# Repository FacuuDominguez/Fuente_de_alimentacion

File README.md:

# Fuente de Alimentación Regulable

 Esta Fuente de Alimentación hecha de manera casera integra de manera embebida un modulo **LM2596** y un **puente rectificador de diodos** haciendo posible la conversión de AC a DC, todo en una misma placa **doble faz** aplicando conocimientos de Electronica tanto de **Corriente Alterna** como **Corriente Continua** 

 ## Caracteristicas

- Integra un modulo LM2596 **Embebido**

- Un puente rectificador de diodos

- Placa de doble cara o **doble faz**

- La tensión que regula es de **1,25V** hasta **20V** DC

- Corriente maxima de salida de **2 A**

- Protección contra inversión de polaridad

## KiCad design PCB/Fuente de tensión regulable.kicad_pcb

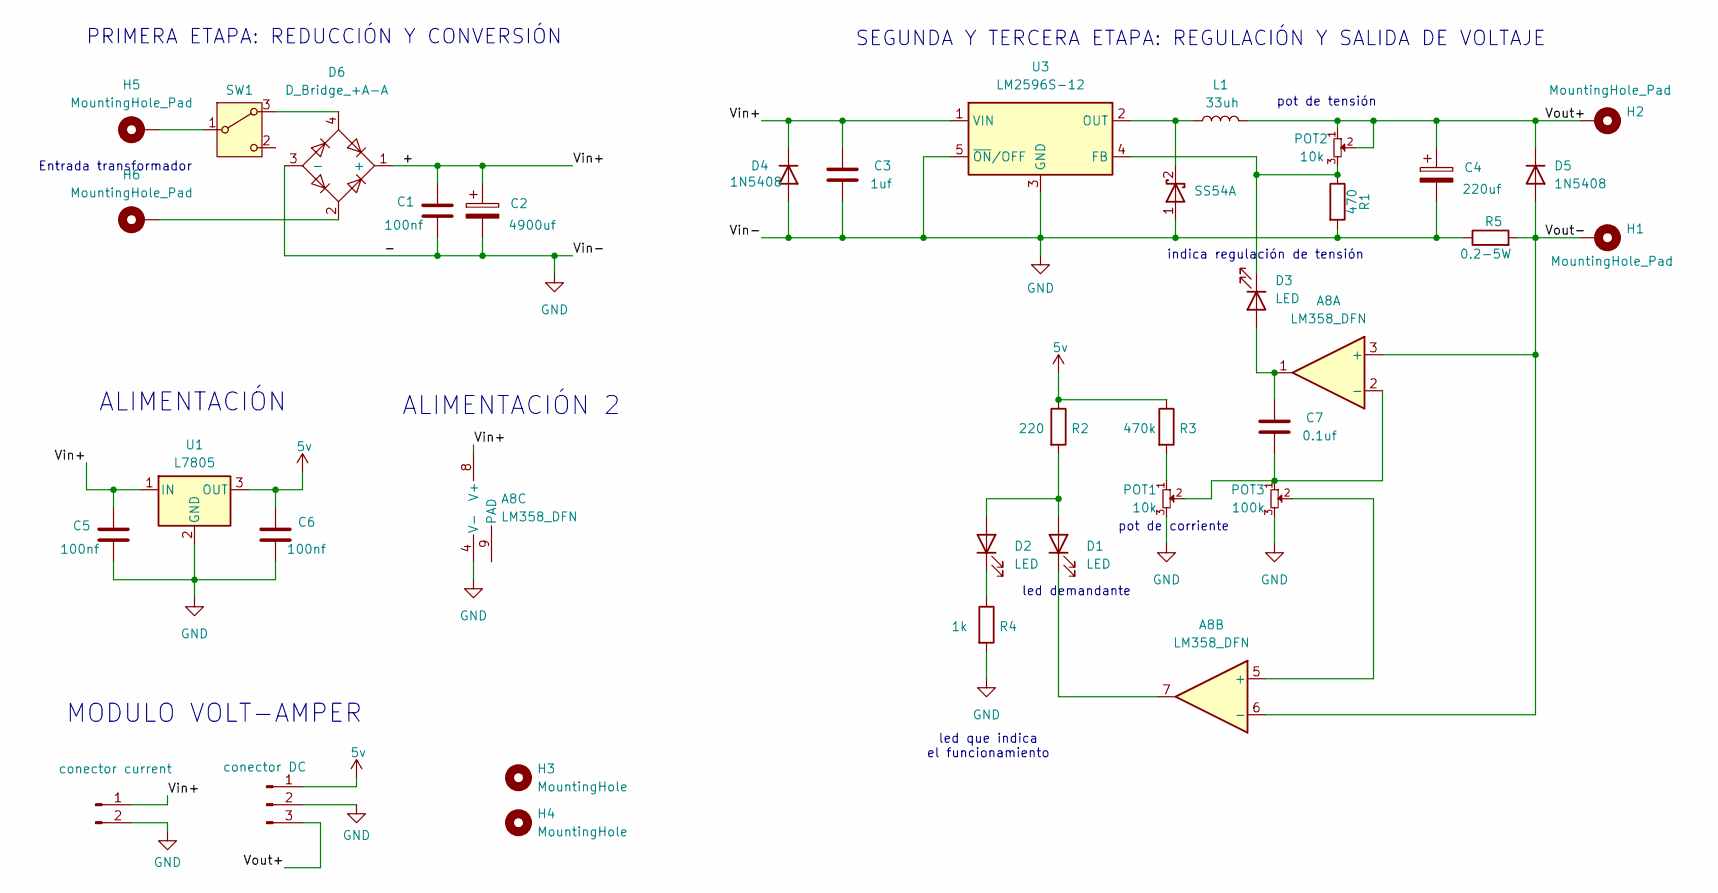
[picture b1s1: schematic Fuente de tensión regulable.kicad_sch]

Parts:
A8: LM358_DFN; Texas_HSOP-8-1EP_3.9x4.9mm_P1.27mm
C1, C5, C6: 100nf; C_0805_2012Metric_Pad1.18x1.45mm_HandSolder
C2: 4900uf; CP_Radial_D22.0mm_P10.00mm_SnapIn
C3: 1uf; C_0805_2012Metric_Pad1.18x1.45mm_HandSolder
C4: 220uf; CP_Elec_10x7.9
C7: 0.1uf; C_0805_2012Metric_Pad1.18x1.45mm_HandSolder
D1, D2, D3: LED; LED_D5.0mm
D4, D5: 1N5408; D_DO-201AE_P5.08mm_Vertical_AnodeUp
D6: D_Bridge_+A-A; Diode_bridge
H1, H2: MountingHole_Pad; MountingHole_2.5mm_Pad
H3, H4: MountingHole; MountingHole_3.2mm_M3_DIN965
H5, H6: MountingHole_Pad; TestPoint_Pad_3.0x3.0mm
J2: conector DC; JST_EH_B3B-EH-A_1x03_P2.50mm_Vertical
J3: conector current; JST_EH_B2B-EH-A_1x02_P2.50mm_Vertical
L1: 33uh; L_Bourns_SRR1260
POT1, POT2: 10k; PinHeader_1x03_P2.54mm_Vertical
POT3: 100k; PinHeader_1x03_P2.54mm_Vertical
R1: 470; R_0805_2012Metric_Pad1.20x1.40mm_HandSolder
R2: 220; R_0805_2012Metric_Pad1.20x1.40mm_HandSolder
R3: 470k; R_0805_2012Metric_Pad1.20x1.40mm_HandSolder
R4: 1k; R_0805_2012Metric_Pad1.20x1.40mm_HandSolder
R5: 0.2-5W; R_Axial_DIN0414_L11.9mm_D4.5mm_P15.24mm_Horizontal
SS54: D_Schottky_Dual_CommonAnode_AKK_Split; D_SMA
SW1: SW_Wuerth_450301014042; PinHeader_1x03_P2.54mm_Vertical
U1: L7805; SOT-223-3_TabPin2
U3: LM2596S-12; TO-263-5_TabPin3

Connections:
5v: C6.1, J2.1, R2.1, R3.1, U1.3 (OUT)
/+: A8.8 (V+), C1.1, C2.1, C3.1, C5.1, D4.1 (K), D6.1 (+), J3.1, U1.1 (IN), U3.1 (VIN)
/Vout+: C4.1, D5.1 (K), H2.1, J2.3, L1.2, POT2.1, POT2.2
/Vout-: A8.3 (+), A8.6 (-), D5.2 (A), H1.1, R5.2
GND: A8.4 (V-), C1.2, C2.2, C3.2, C4.2, C5.2, C6.2, D4.2 (A), D6.3 (-), J2.2, J3.2, POT1.3, POT3.3, R1.2, R4.2, R5.1, SS54.1 (A), U1.2 (GND), U3.3 (GND), U3.5 (~ON/OFF)
unnamed: A8.2 (-), C7.2, POT1.2, POT3.1
unnamed: A8.5 (+), POT3.2
unnamed: D1.2 (A), D2.2 (A), R2.2
unnamed: A8.7, D1.1 (K)
unnamed: D2.1 (K), R4.1
unnamed: A8.1, C7.1, D3.2 (A)
unnamed: D3.1 (K), POT2.3, R1.1, U3.4 (FB)
unnamed: D6.2, H6.1
unnamed: POT1.1, R3.2
unnamed: L1.1, SS54.2 (K), U3.2 (OUT)
unnamed: D6.4, SW1.3 (A)
unnamed: H5.1, SW1.1 (B)

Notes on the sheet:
ALIMENTACIÓN 2
pot de tensión
indica regulación de tensión
led que indica el funcionamiento
ALIMENTACIÓN
PRIMERA ETAPA: REDUCCIÓN Y CONVERSIÓN
MODULO VOLT-AMPER
SEGUNDA Y TERCERA ETAPA: REGULACIÓN Y SALIDA DE VOLTAJE
Entrada transformador
pot de corriente
led demandante

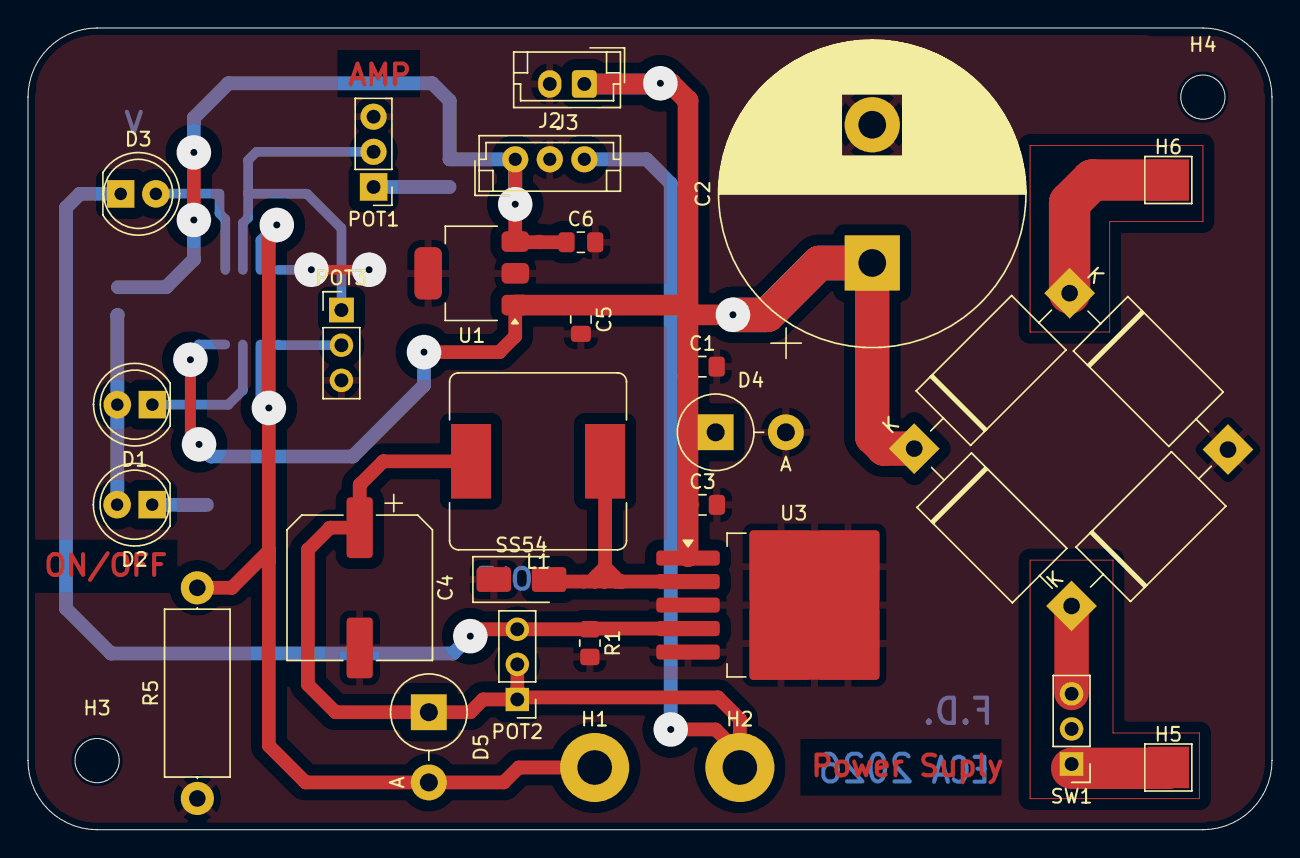
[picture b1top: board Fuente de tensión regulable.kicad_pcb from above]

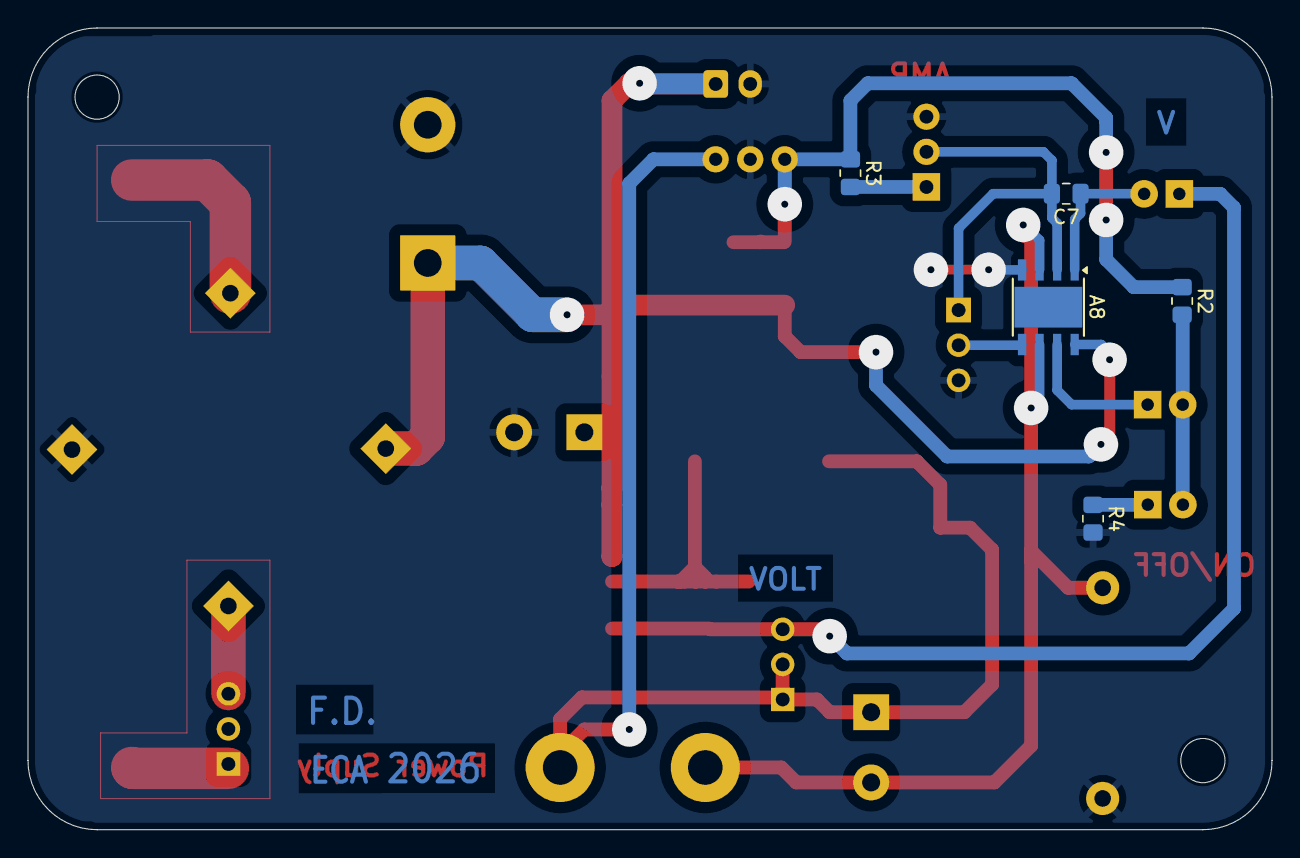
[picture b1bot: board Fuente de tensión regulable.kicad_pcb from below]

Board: 2 copper layers, 90.0 x 58.0 mm, 35 parts (5 on the bottom side), 17 nets.

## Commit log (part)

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2026-06-09 Create a
